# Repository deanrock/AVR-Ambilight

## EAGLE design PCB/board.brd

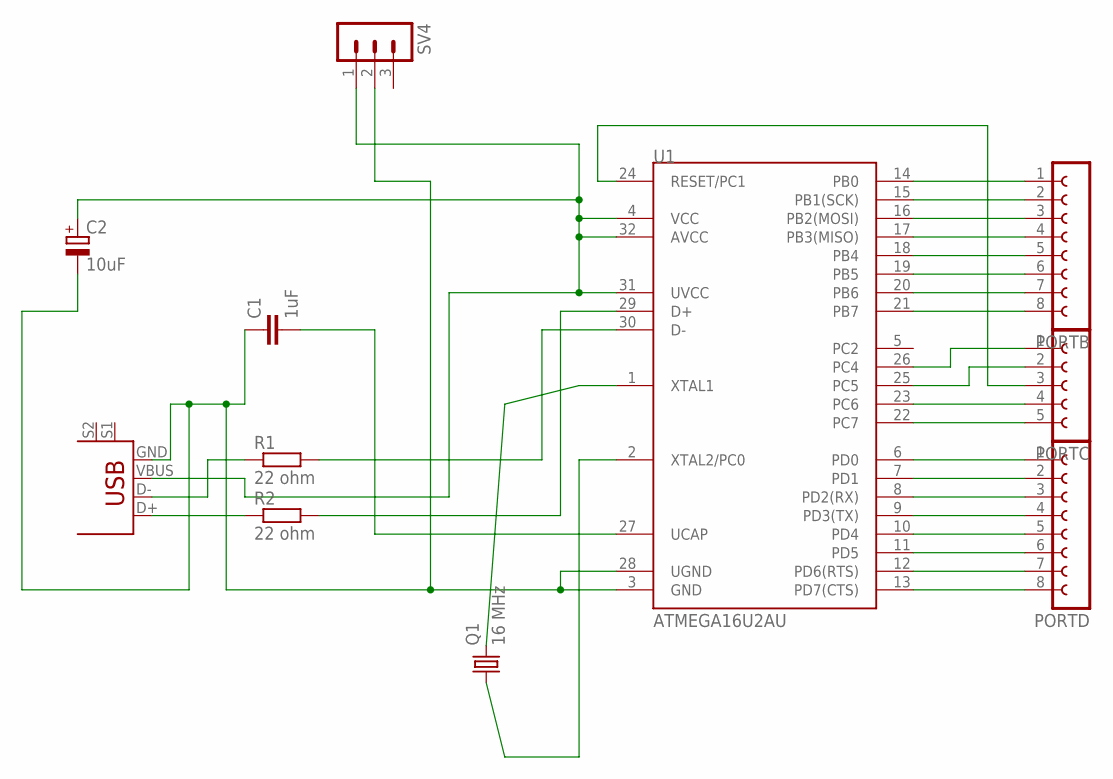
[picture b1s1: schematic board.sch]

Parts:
C1: 1uF; C025-024X044
C2: 10uF; E1,8-4
PORTB: FE08-1; FE08
PORTC: FE05-1
PORTD: FE08-1; FE08
Q1: 16 MHz; HC49/S
R1, R2: 22 ohm; 0207/5V
SV4: MA03-1
U1: ATMEGA16U2AU; TQFP32-08
U$2: USB+SHIELD; USB-B-PTH

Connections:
unnamed: R1.1, U$2.D-
unnamed: PORTD.6, U1.11 (PD5)
unnamed: R2.1, U$2.D+
unnamed: R1.2, U1.30 (D-)
unnamed: PORTB.2, U1.15 (PB1(SCK))
unnamed: C2.+, SV4.1, U1.4 (VCC), U1.31 (UVCC), U1.32 (AVCC), U$2.VBUS
unnamed: PORTB.4, U1.17 (PB3(MISO))
unnamed: Q1.2, U1.1 (XTAL1)
unnamed: Q1.1, U1.2 (XTAL2/PC0)
unnamed: C1.2, U1.27 (UCAP)
unnamed: R2.2, U1.29 (D+)
unnamed: PORTB.1, U1.14 (PB0)
unnamed: PORTB.5, U1.18 (PB4)
unnamed: PORTB.6, U1.19 (PB5)
unnamed: PORTB.7, U1.20 (PB6)
unnamed: PORTB.8, U1.21 (PB7)
unnamed: PORTD.8, U1.13 (PD7(CTS))
unnamed: PORTC.2, U1.25 (PC5)
unnamed: PORTC.1, U1.26 (PC4)
unnamed: PORTC.4, U1.23 (PC6)
unnamed: PORTC.5, U1.22 (PC7)
unnamed: PORTD.7, U1.12 (PD6(RTS))
unnamed: PORTD.5, U1.10 (PD4)
unnamed: PORTD.4, U1.9 (PD3(TX))
unnamed: PORTD.3, U1.8 (PD2(RX))
unnamed: PORTD.2, U1.7 (PD1)
unnamed: PORTD.1, U1.6 (PD0)
unnamed: C1.1, C2.-, SV4.2, U1.3 (GND), U1.28 (UGND), U$2.GND
unnamed: PORTB.3, U1.16 (PB2(MOSI))
unnamed: PORTC.3, U1.24 (RESET/PC1)

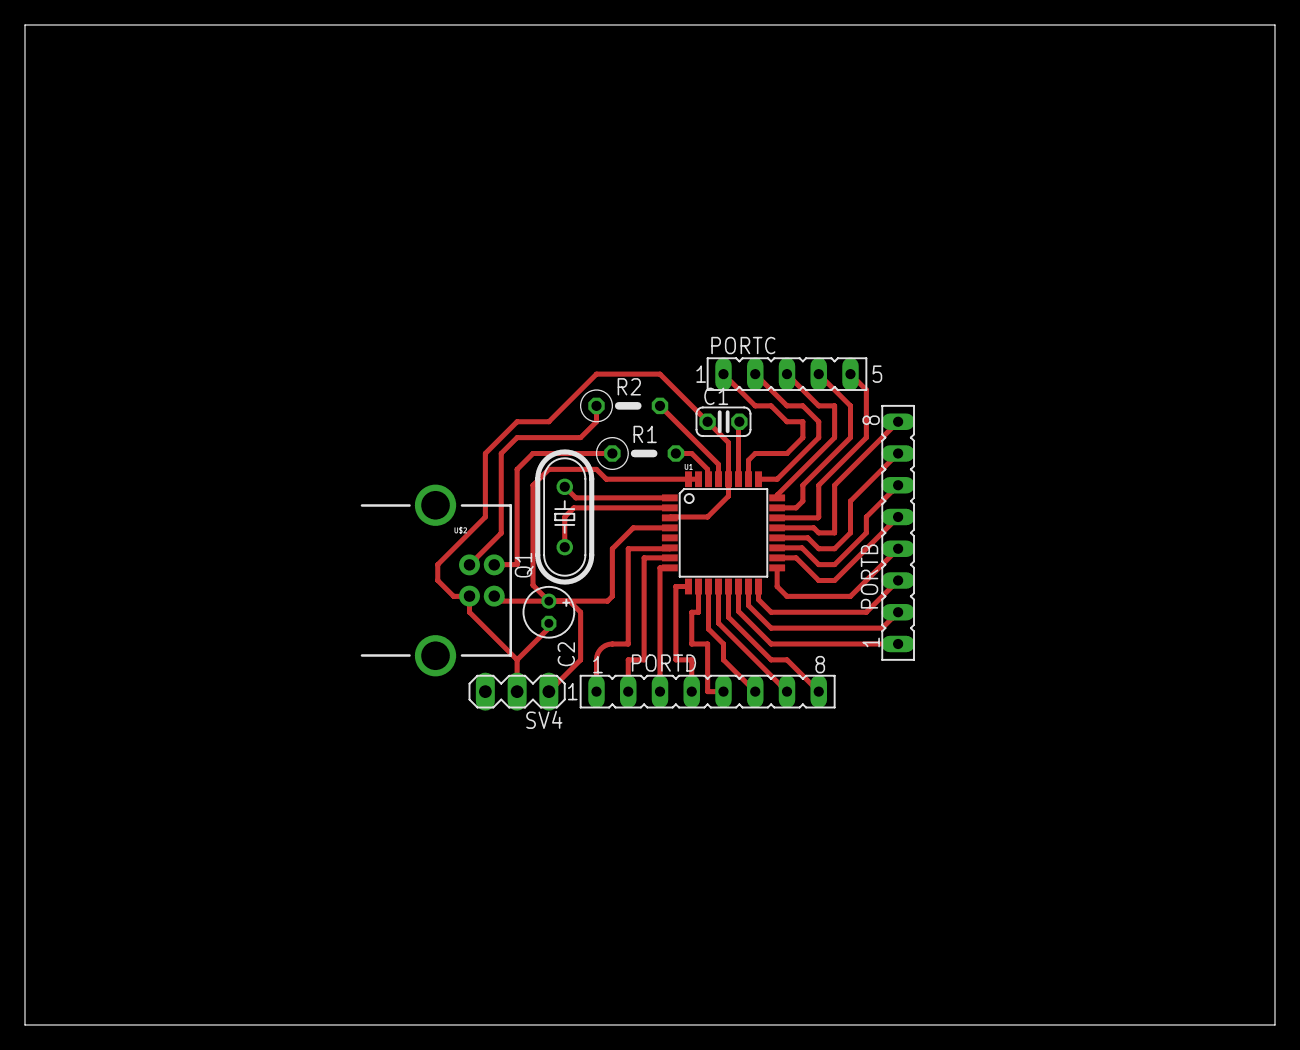
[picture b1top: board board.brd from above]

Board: 2 copper layers, 100.0 x 80.0 mm, 11 parts (0 on the bottom side), 30 nets.

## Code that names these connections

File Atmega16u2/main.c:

#include <avr/io.h>
#include <util/delay.h>
#include <avr/interrupt.h>  

#define SPI_PORT PORTB
#define SPI_DDR  DDRB
#define SPI_CS   PB2

#define SPI_CLOCK_MASK 0x03
#define SPI_2XCLOCK_MASK 0x01

#define SPI_MODE_MASK 0x0C 
#define output_low(port,pin) port &= ~(1<<pin)
#define output_high(port,pin) port |= (1<<pin)
#define set_input(portdir,pin) portdir &= ~(1<<pin)
#define set_output(portdir,pin) portdir |= (1<<pin)

volatile int diodes[25*3];
volatile int current=0;
volatile int time=0;

int main (void)
{
	//spi
	/*int bittimer = ( F_CPU / 128000 / 16 ) - 1;
	SPI_DDR = (1<<PB3)|(1<<PB5)|(1<<PB2);

	SPCR |= _BV(MSTR);
	SPCR |= _BV(SPE);

	SPCR &= ~(_BV(DORD));
	SPCR = (SPCR & ~SPI_MODE_MASK) | 0x00;

	SPCR = (SPCR & ~SPI_CLOCK_MASK) | (0x01 & SPI_CLOCK_MASK);
	SPSR = (SPSR & ~SPI_2XCLOCK_MASK) | ((0x01 >> 2) & SPI_2XCLOCK_MASK);
	SPCR &= ~(_BV(DORD));
  
	//serial
	/* Set the baud rate 
	UBRR0H = (unsigned char) (bittimer >> 8);
	UBRR0L = (unsigned char) bittimer;
	/* set the framing to 8N1 
	UCSR0C = (3 << UCSZ00);
	/* Engage! 
	UCSR0B = (1 << RXEN0) | (1 << TXEN0) | (1 << RXCIE0 );
	
  
	//timer
	TIMSK0 = _BV(OCIE0A);  // Enable Interrupt TimerCounter0 Compare Match A (SIG_OUTPUT_COMPARE0A)
	TCCR0A = _BV(WGM01);  // Mode = CTC
	TCCR0B = _BV(CS02) | _BV(CS00);   // Clock/1024, 0.001024 seconds per tick
	OCR0A = 244;          // 0.001024*244 ~= .25 SIG_OUTPUT_COMPARE0A will be triggered 4 times per second.

	sei();*/
	set_output(DDRB, PB0);
	
	while(1) {
		_delay_ms(500);
		output_high(PORTB, PB0);
		_delay_ms(500);
		output_low(PORTB, PB0);
		
	}
	
   return 0;
}

ISR (SIG_OUTPUT_COMPARE0A)
{
	int i=0;
	time++;
	
	if(time > 4*30) {
		for(i = 0;i<25;i++) {
			for(SPDR = 0x00; !(SPSR & _BV(SPIF)); );
			for(SPDR = 0x00; !(SPSR & _BV(SPIF)); );
			for(SPDR = 0x00; !(SPSR & _BV(SPIF)); );
		}
		
		current=0;
		time=0;
	}
}
/*
ISR(SIG_USART_RECV) 
{ 
	char ReceivedByte;
	int i;
	
	ReceivedByte = UDR0;

	diodes[current++]=ReceivedByte;
	time=0;

	if(current>=25*3) {
		current=0;
		for(i = 0;i<25*3;i++) {
			for(SPDR = diodes[i]; !(SPSR & _BV(SPIF)); );
		}
	}
}
*/

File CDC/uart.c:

/* Name: uart.c
 * Project: AVR USB driver for CDC interface on Low-Speed USB
 * Author: Osamu Tamura
 * Creation Date: 2006-06-18
 * Tabsize: 4
 * Copyright: (c) 2006 by Recursion Co., Ltd.
 * License: Proprietary, free under certain conditions. See Documentation.
 *
 * 2006-07-08   adapted to higher baudrate by T.Kitazawa
 */
/*
General Description:
    This module implements the UART rx/tx system of the USB-CDC driver.
*/

#include <avr/io.h>
#include <avr/interrupt.h>
#include <avr/pgmspace.h>   /* needed by usbdrv.h */
#include "oddebug.h"
#include "usbdrv.h"
#include "uart.h"

extern uchar    sendEmptyFrame;

/* UART buffer */
uchar    urptr, uwptr, irptr, iwptr;
uchar    rx_buf[RX_SIZE+HW_CDC_BULK_IN_SIZE], tx_buf[TX_SIZE];


void uartInit(ulong baudrate, uchar parity, uchar stopbits, uchar databits)
{
usbDWord_t   br;

    br.dword = ((F_CPU>>3)+(baudrate>>1)) / baudrate - 1;
	UCSR0A  |= (1<<U2X0);

#if DEBUG_LEVEL < 1
    /*    USART configuration    */
    UCSR0B  = 0;
    UCSR0C  = URSEL_MASK | ((parity==1? 3:parity)<<UPM00) | ((stopbits>>1)<<USBS0) | ((databits-5)<<UCSZ00);
    UBRR0L  = br.bytes[0];
    UBRR0H  = br.bytes[1];
#else
    DBG1(0xf0, br.bytes, 2);
#endif /* DEBUG_LEVEL */

    UCSR0B  = (1<<RXEN0) | (1<<TXEN0);

	UART_CTRL_DDR	= (1<<UART_CTRL_DTR) | (1<<UART_CTRL_RTS);
	UART_CTRL_PORT	= 0xff;

#ifdef UART_INVERT
	DDRB	|= (1<<PB1)|(1<<PB0);
	PCMSK1	|= (1<<PCINT9)|(1<<PCINT8);
	PCICR	|= (1<<PCIE1);
#endif
}

void uartPoll(void)
{
	uchar		next;

	/*  device => RS-232C  */
	while( (UCSR0A&(1<<UDRE0)) && uwptr!=irptr && (UART_CTRL_PIN&(1<<UART_CTRL_CTS)) ) {
        UDR0    = tx_buf[irptr];
        irptr   = (irptr+1) & TX_MASK;

        if( usbAllRequestsAreDisabled() && uartTxBytesFree()>HW_CDC_BULK_OUT_SIZE ) {
            usbEnableAllRequests();
        }
    }

	/*  device <= RS-232C  */
	while( UCSR0A&(1<<RXC0) ) {
	    next = (iwptr+1) & RX_MASK;
		if( next!=urptr ) {
	        uchar   status, data;

	        status  = UCSR0A;
	        data    = UDR0;
	        status  &= (1<<FE0) | (1<<DOR0) | (1<<UPE0);
	        if(status == 0) { /* no receiver error occurred */
	            rx_buf[iwptr] = data;
	            iwptr = next;
	        }
		}
		else {
			UART_CTRL_PORT	&= ~(1<<UART_CTRL_RTS);
			break;
		}
    }

	/*  USB <= device  */
    if( usbInterruptIsReady() && (iwptr!=urptr || sendEmptyFrame) ) {
        uchar   bytesRead, i;

        bytesRead = (iwptr-urptr) & RX_MASK;
        if(bytesRead>HW_CDC_BULK_IN_SIZE)
            bytesRead = HW_CDC_BULK_IN_SIZE;
		next	= urptr + bytesRead;
		if( next>=RX_SIZE ) {
			next &= RX_MASK;
			for( i=0; i<next; i++ )
				rx_buf[RX_SIZE+i]	= rx_buf[i];
		}
        usbSetInterrupt(rx_buf+urptr, bytesRead);
        urptr   = next;
		if( bytesRead )
			UART_CTRL_PORT	|= (1<<UART_CTRL_RTS);

        /* send an empty block after last data block to indicate transfer end */
        sendEmptyFrame = (bytesRead==HW_CDC_BULK_IN_SIZE && iwptr==urptr)? 1:0;
    }
}


#ifdef UART_INVERT
/*
	enables software-inverter (PC0 -|>o- PB0, PC1 -|>o- PB1)
	to connect to RS-232C line directly. ( <= 2400 bps )
	(atmega48/88 only)
*/
ISR( PCINT1_vect, ISR_NAKED )
{
	asm volatile(
		"out	%0, r16"    	"\n\t"
		"in		r16, __SREG__"	"\n\t"
		"out	%1, r16"    	"\n\t"

		"in		r16, %2"    	"\n\t"
        "com    r16"    		"\n\t"
		"out	%3, r16"    	"\n\t"

		"in		r16, %1"    	"\n\t"
		"out	__SREG__, r16"	"\n\t"
		"in		r16, %0"    	"\n\t"
         :
         : "I" (_SFR_IO_ADDR(GPIOR0)),
           "I" (_SFR_IO_ADDR(GPIOR1)),
           "I" (_SFR_IO_ADDR(PINC)),
           "I" (_SFR_IO_ADDR(PORTB))
        );

	reti();
}
#endif

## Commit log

2012-05-31 initial PCB
2012-06-03 fixed PCB design
2012-06-03 fixed device name
2012-06-09 added test code for Atmega16u2

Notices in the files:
parts and their libraries:
SparkFun: Licensing: CC v3.0 Share-Alike You are welcome to use this library for commercial purposes.
